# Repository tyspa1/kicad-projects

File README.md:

# Kicad Projects
By Tyler Spadgenske</br>
GPL v2 copyright :copyright: 2016

## Projects in this Repository
*1. LED Dice*
Project using a 555 timer, binary counter, and 74xx logic chips to create a random die simulation.</br>
*2. Battery Charger*
Lithium Ion Battery charger using a MCP73831/2 over micro USB

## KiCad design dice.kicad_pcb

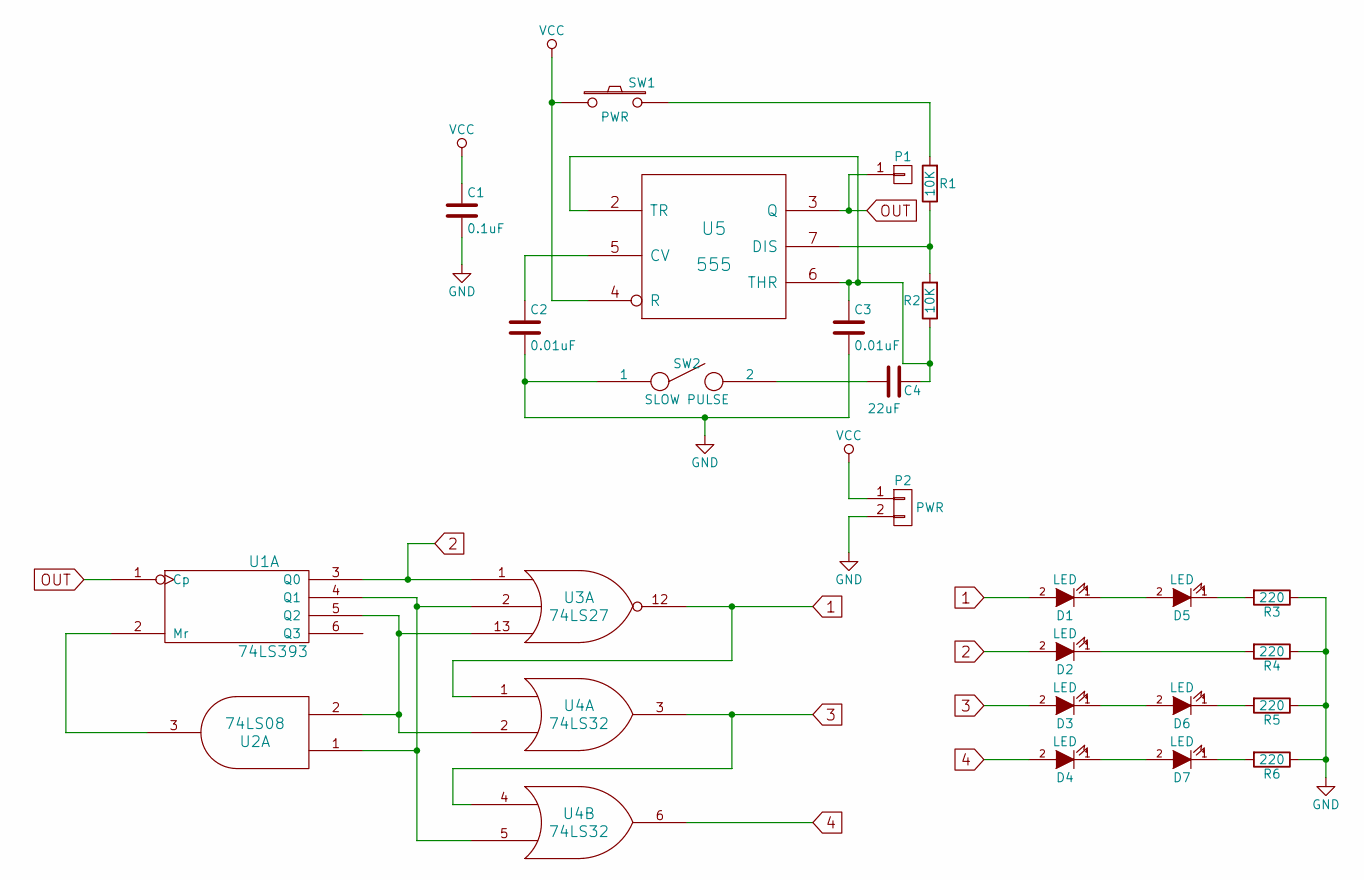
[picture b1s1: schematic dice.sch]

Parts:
C1: 0.1uF; C_1206
C2, C3: 0.01uF; C_1206
C4: 22uF; C_1206
D1, D2, D3, D4, D5, D6, D7: LED; LED-5MM
P1: CONN_01X01; Socket_Strip_Straight_1x01
P2: PWR
R1, R2: 10K; C_1206
R3, R4, R5, R6: 220; C_1206
SW1: PWR; LED-5MM
SW2: SLOW PULSE; Socket_Strip_Straight_1x03
U1: 74LS393; SOIC-14_3.9x8.7mm_Pitch1.27mm
U2: 74LS08; SOIC-14_3.9x8.7mm_Pitch1.27mm
U3: 74LS27; SOIC-14_3.9x8.7mm_Pitch1.27mm
U4: 74LS32; SOIC-14_3.9x8.7mm_Pitch1.27mm
U5: 555; SOIC-8_3.9x4.9mm_Pitch1.27mm

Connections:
1: D1.2 (A), U3.12, U4.1
2: D2.2 (A), U1.3 (Q0), U3.1
3: D3.2 (A), U4.3, U4.4
4: D4.2 (A), U4.6
GND: C1.2, C2.2, C3.2, P2.2, R3.1, R4.1, R5.1, R6.1, SW2.1, U1.7 (GND), U2.7 (GND), U3.7 (GND), U4.7 (GND), U5.1 (GND); also elsewhere on the board
unnamed: C2.1, U5.5 (CV)
unnamed: C3.1, C4.1, R2.1, U5.2 (TR), U5.6 (THR)
unnamed 7: C4.2, SW2.2; also elsewhere on the board
unnamed: D1.1 (K), D5.2 (A)
unnamed: D2.1 (K), R4.2
unnamed: D3.1 (K), D6.2 (A)
unnamed: D4.1 (K), D7.2 (A)
unnamed: D5.1 (K), R3.2
unnamed: D6.1 (K), R5.2
unnamed: D7.1 (K), R6.2
unnamed: R1.1, R2.2, U5.7 (DIS)
unnamed: R1.2, SW1.2
unnamed: U1.2 (Mr), U2.3
unnamed: U1.4 (Q1), U2.1, U3.2, U4.5
unnamed: U1.5 (Q2), U2.2, U3.13, U4.2
OUT: P1.1, U1.1 (Cp), U5.3 (Q)
VCC: C1.1, P2.1, SW1.1, U1.14 (VCC), U2.14 (VCC), U3.14 (VCC), U4.14 (VCC), U5.4 (R), U5.8 (VCC)

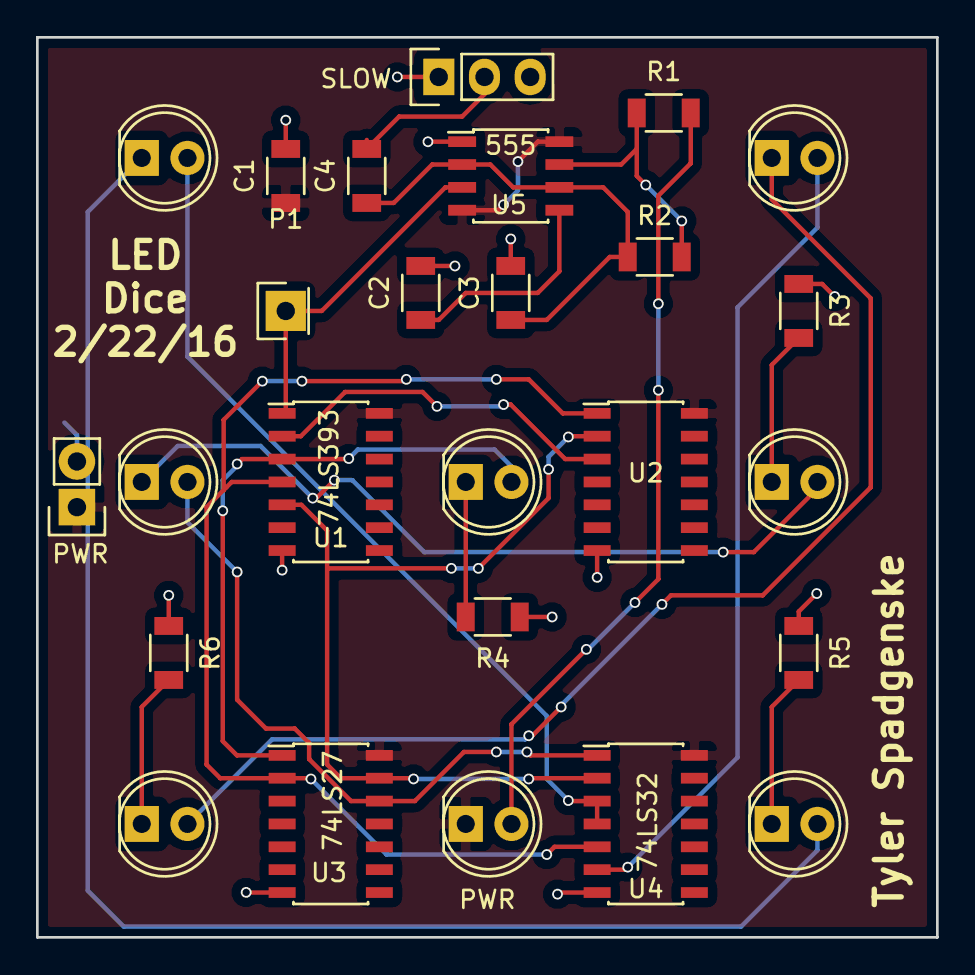
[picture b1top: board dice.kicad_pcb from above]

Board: 2 copper layers, 50.0 x 50.0 mm, 26 parts (0 on the bottom side), 22 nets.

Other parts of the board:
SLOW: SLOW PULSE; Socket_Strip_Straight_1x03

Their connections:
GND: SLOW.1; also elsewhere on the board
unnamed 7: SLOW.2; also elsewhere on the board

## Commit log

2016-02-22 :octocat: Added .gitattributes & .gitignore files
2016-02-22 dice project v0.00001
2016-02-22 :cactus: :camel:
2016-02-22 v1 done :smile:
2016-03-24 New Format, fixes :sailboat:
2016-07-19 Added project
2016-12-13 added ili9341 breakout
